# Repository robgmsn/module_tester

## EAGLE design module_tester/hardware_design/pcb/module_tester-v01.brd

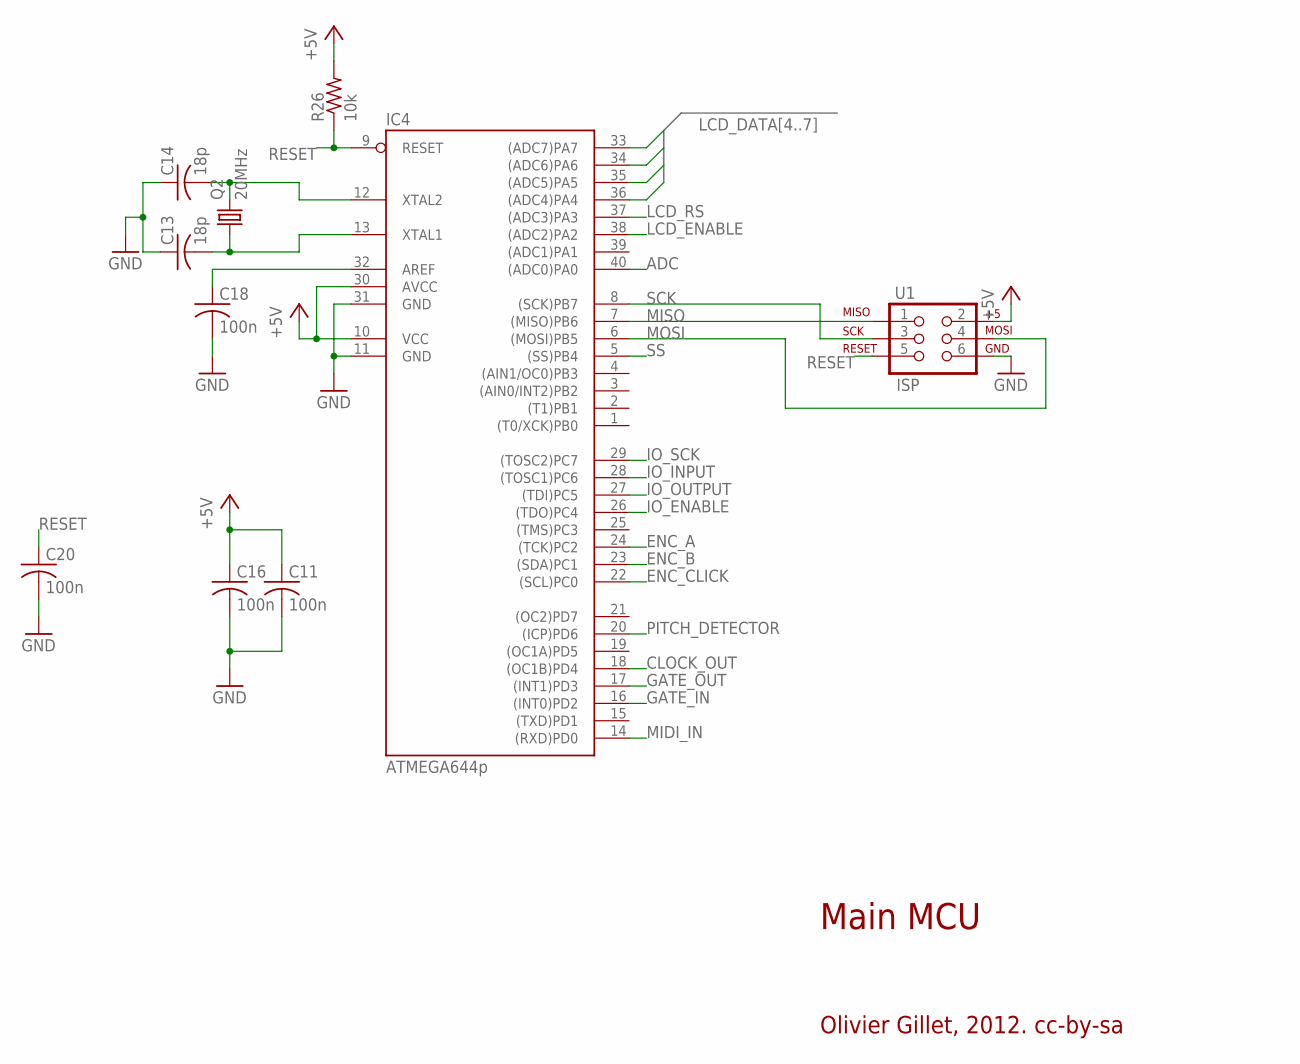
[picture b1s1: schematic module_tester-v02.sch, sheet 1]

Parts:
C11, C16, C18, C20: 100n; C025-025X050
C13, C14: 18p; C025-025X050
IC4: ATMEGA644p; DIL40
Q2: 20MHz; HC49U-V
R26: 10k; 0204/7
U1: ISP; 2X3

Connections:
+5V: C11.1, C16.1, IC4.10 (VCC), IC4.30 (AVCC), R26.2, U1.2; also elsewhere on the board
ADC: IC4.40 ((ADC0)PA0); also elsewhere on the board
CLOCK_OUT: IC4.18 ((OC1B)PD4); also elsewhere on the board
ENC_A: IC4.24 ((TCK)PC2); also elsewhere on the board
ENC_B: IC4.23 ((SDA)PC1); also elsewhere on the board
ENC_CLICK: IC4.22 ((SCL)PC0); also elsewhere on the board
GATE_IN: IC4.16 ((INT0)PD2); also elsewhere on the board
GATE_OUT: IC4.17 ((INT1)PD3); also elsewhere on the board
GND: C11.2, C13.1, C14.1, C16.2, C18.2, C20.2, IC4.11 (GND), IC4.31 (GND), U1.6; also elsewhere on the board
IO_ENABLE: IC4.26 ((TDO)PC4); also elsewhere on the board
IO_INPUT: IC4.28 ((TOSC1)PC6); also elsewhere on the board
IO_OUTPUT: IC4.27 ((TDI)PC5); also elsewhere on the board
IO_SCK: IC4.29 ((TOSC2)PC7); also elsewhere on the board
LCD_DATA4: IC4.36 ((ADC4)PA4); also elsewhere on the board
LCD_DATA5: IC4.35 ((ADC5)PA5); also elsewhere on the board
LCD_DATA6: IC4.34 ((ADC6)PA6); also elsewhere on the board
LCD_DATA7: IC4.33 ((ADC7)PA7); also elsewhere on the board
LCD_ENABLE: IC4.38 ((ADC2)PA2); also elsewhere on the board
LCD_RS: IC4.37 ((ADC3)PA3); also elsewhere on the board
MIDI_IN: IC4.14 ((RXD)PD0); also elsewhere on the board
MISO: IC4.7 ((MISO)PB6), U1.1
MOSI: IC4.6 ((MOSI)PB5), U1.4; also elsewhere on the board
unnamed: C18.1, IC4.32 (AREF)
unnamed: C13.2, IC4.13 (XTAL1), Q2.1
unnamed: C14.2, IC4.12 (XTAL2), Q2.2
PITCH_DETECTOR: IC4.20 ((ICP)PD6); also elsewhere on the board
RESET: C20.1, IC4.9 (RESET), R26.1, U1.5
SCK: IC4.8 ((SCK)PB7), U1.3; also elsewhere on the board
SS: IC4.5 ((SS)PB4); also elsewhere on the board

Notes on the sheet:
Main MCU
Olivier Gillet, 2012. cc-by-sa

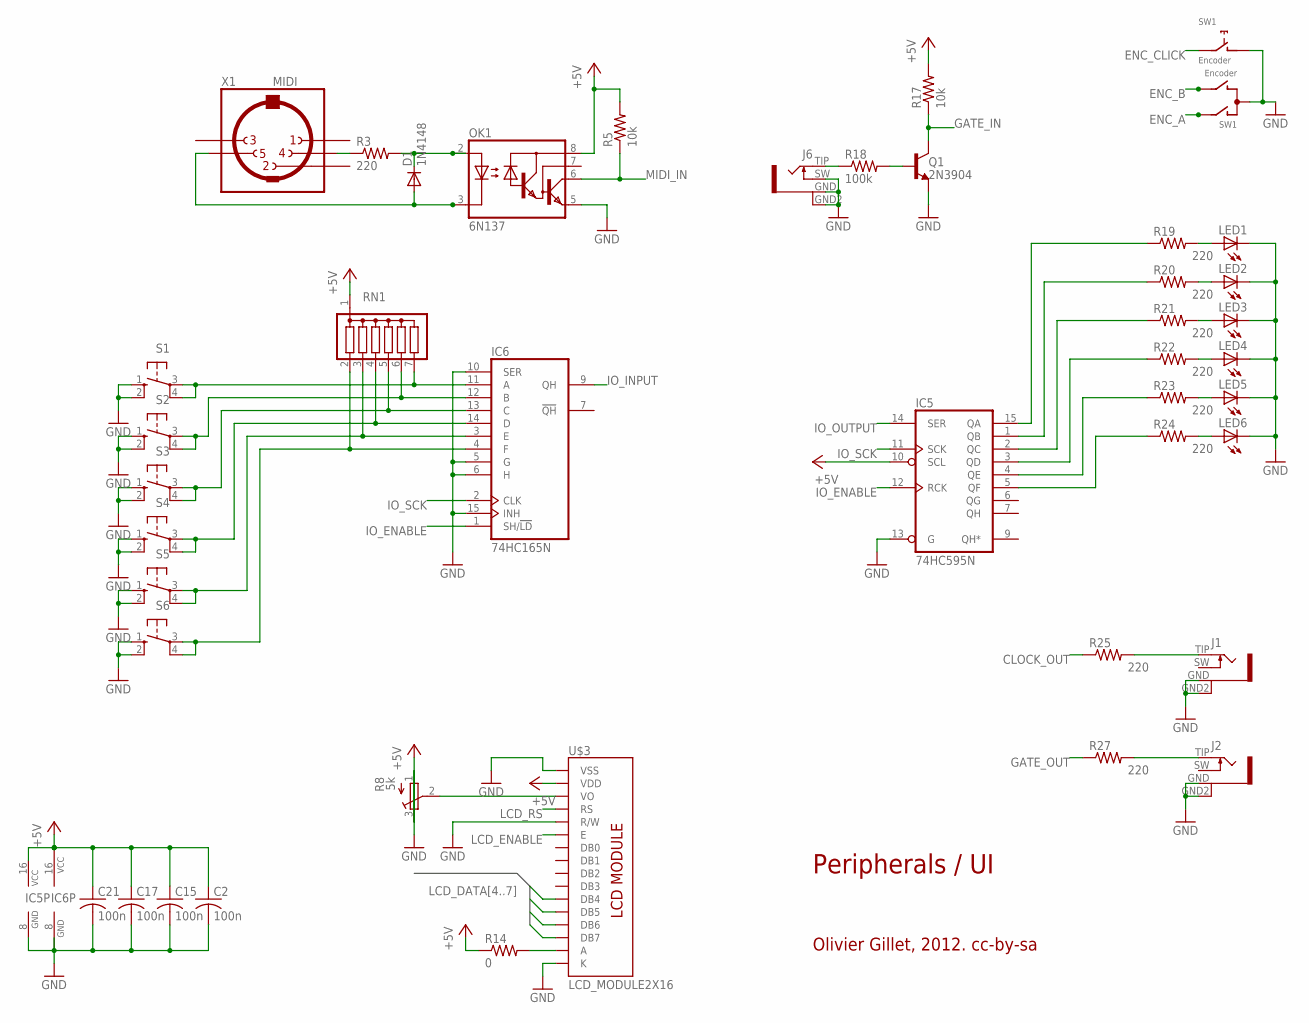
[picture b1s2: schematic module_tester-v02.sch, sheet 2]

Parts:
C2, C15, C17, C21: 100n; C025-025X050
D1: 1N4148; D-5
IC5: 74HC595N; DIL16
IC6: 74HC165N; DIL16
J1, J2, J6: PJ301WQP; WQP_PJ_301BM
LED1, LED2, LED3, LED4, LED5, LED6: LED3MM
OK1: 6N137; DIL08
Q1: 2N3904; TO92-
R3, R19, R20, R21, R22, R23, R24, R25, R27: 220; 0204/7
R5, R17: 10k; 0204/7
R8: 5k; RTRIM3296W
R14: 0; 0204/7
R18: 100k; 0204/7
RN1: G06R; SIL7
S1, S2, S3, S4, S5, S6: 40-XX; B3F-40XX
SW1: Encoder; ALPS_EC12E_SW
U$3: LCD_MODULE2X16; LCD_MODULE_2X16
X1: MIDI; MAB5SH

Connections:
+5V: C2.1, C15.1, C17.1, C21.1, IC5.10 (SCL), IC5.16 (VCC), IC6.16 (VCC), OK1.8 (VCC), R5.2, R8.3 (E), R14.1, R17.2, RN1.1, U$3.2 (VDD); also elsewhere on the board
CLOCK_OUT: R25.1; also elsewhere on the board
ENC_A: SW1.A; also elsewhere on the board
ENC_B: SW1.B; also elsewhere on the board
ENC_CLICK: SW1.E (2); also elsewhere on the board
GATE_IN: Q1.1 (C), R17.1; also elsewhere on the board
GATE_OUT: R27.1; also elsewhere on the board
GND: C2.2, C15.2, C17.2, C21.2, IC5.8 (GND), IC5.13 (G), IC6.5 (G), IC6.6 (H), IC6.8 (GND), IC6.10 (SER), IC6.15 (INH), J1.GND (1), J1.GND2 (4), J2.GND (1), J2.GND2 (4), J6.GND (1), J6.GND2 (4), J6.SW (3), LED1.K (C), LED2.K (C), LED3.K (C), LED4.K (C), LED5.K (C), LED6.K (C), OK1.5 (GND), Q1.3 (E), R8.1 (A), S1.1 (S), S1.2 (S1), S2.1 (S), S2.2 (S1), S3.1 (S), S3.2 (S1), S4.1 (S), S4.2 (S1), S5.1 (S), S5.2 (S1), S6.1 (S), S6.2 (S1), SW1.C, SW1.D (1), U$3.1 (VSS), U$3.5 (R/W), U$3.16 (K); also elsewhere on the board
IO_ENABLE: IC5.12 (RCK), IC6.1 (SH/!LD); also elsewhere on the board
IO_INPUT: IC6.9 (QH); also elsewhere on the board
IO_OUTPUT: IC5.14 (SER); also elsewhere on the board
IO_SCK: IC5.11 (SCK), IC6.2 (CLK); also elsewhere on the board
LCD_DATA4: U$3.11 (DB4); also elsewhere on the board
LCD_DATA5: U$3.12 (DB5); also elsewhere on the board
LCD_DATA6: U$3.13 (DB6); also elsewhere on the board
LCD_DATA7: U$3.14 (DB7); also elsewhere on the board
LCD_ENABLE: U$3.6 (E); also elsewhere on the board
LCD_RS: U$3.4 (RS); also elsewhere on the board
MIDI_IN: OK1.6 (VO), R5.1; also elsewhere on the board
unnamed: IC5.2 (QC), R21.1
unnamed: IC5.4 (QE), R23.1
unnamed: LED5.A, R23.2
unnamed: J6.TIP (2), R18.1
unnamed: IC6.3 (E), RN1.3, S5.3, S5.4 (P1)
unnamed: J1.TIP (2), R25.2
unnamed: IC6.4 (F), RN1.2, S6.3, S6.4 (P1)
unnamed: IC6.14 (D), RN1.4, S4.3, S4.4 (P1)
unnamed: J2.TIP (2), R27.2
unnamed: R8.2 (S), U$3.3 (VO)
unnamed: LED6.A, R24.2
unnamed: IC5.5 (QF), R24.1
unnamed: IC6.11 (A), RN1.7, S1.3, S1.4 (P1)
unnamed: D1.C, OK1.2 (A), R3.2
unnamed: IC5.15 (QA), R19.1
unnamed: IC5.1 (QB), R20.1
unnamed: IC5.3 (QD), R22.1
unnamed: LED1.A, R19.2
unnamed: LED2.A, R20.2
unnamed: LED3.A, R21.2
unnamed: LED4.A, R22.2
unnamed: Q1.2 (B), R18.2
unnamed: R3.1, X1.4
unnamed: D1.A, OK1.3 (C), X1.5
unnamed: R14.2, U$3.15 (A)
unnamed: IC6.12 (B), RN1.6, S2.3, S2.4 (P1)
unnamed: IC6.13 (C), RN1.5, S3.3, S3.4 (P1)

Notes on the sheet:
Peripherals / UI
Olivier Gillet, 2012. cc-by-sa

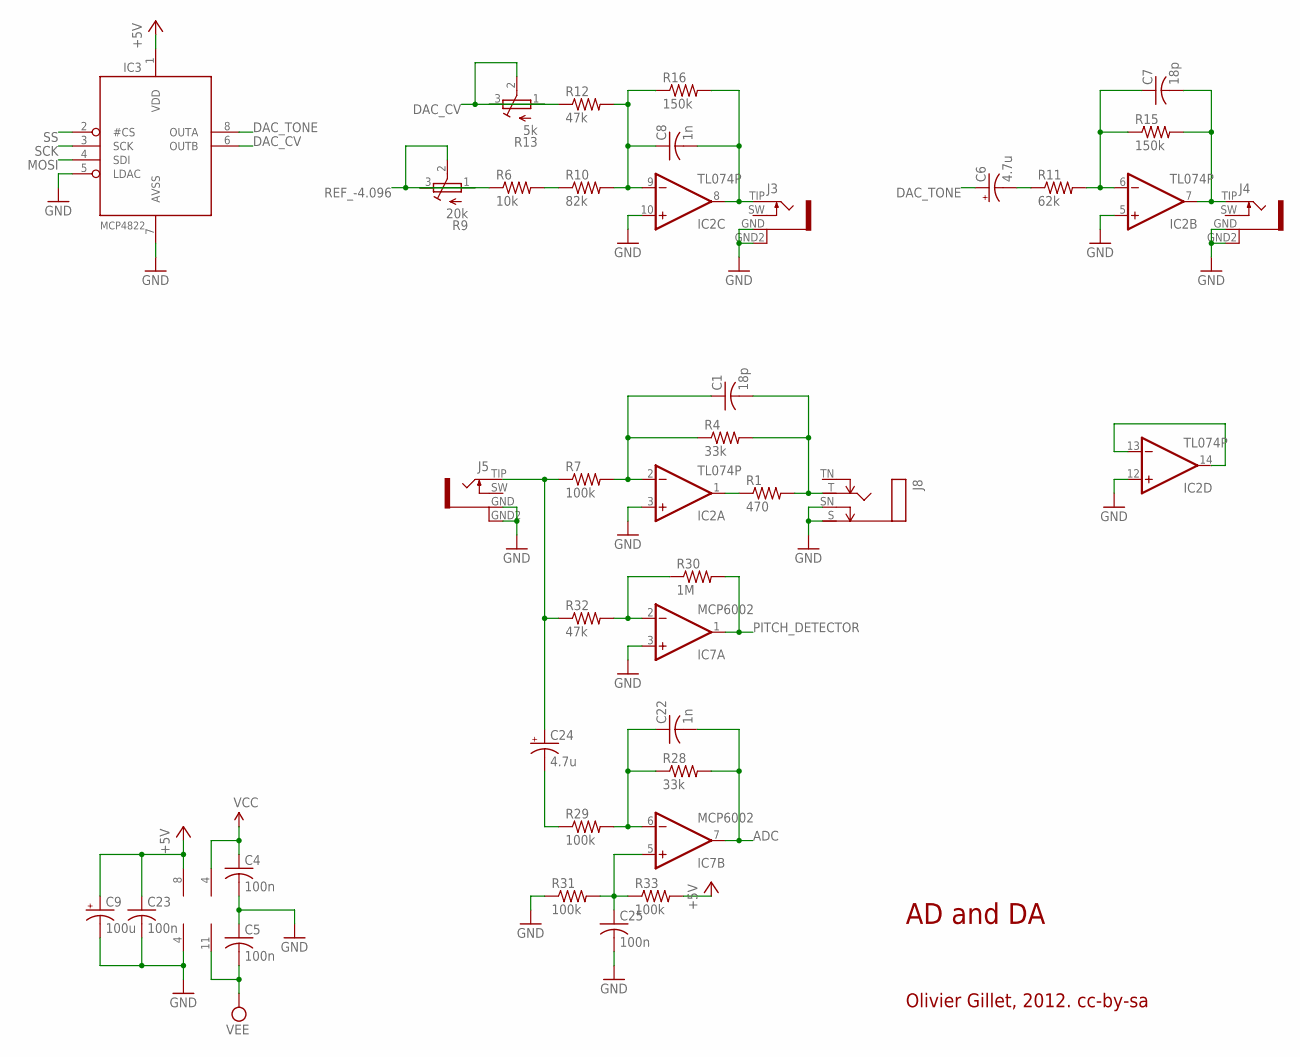
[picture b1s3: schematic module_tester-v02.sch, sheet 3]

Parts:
C1, C7: 18p; C025-025X050
C4, C5, C23, C25: 100n; C025-025X050
C6, C24: 4.7u; E2,5-6
C8, C22: 1n; C025-025X050
C9: 100u; E2,5-7
IC2: TL074P; DIL14
IC3: MCP4822; DIL08
IC7: MCP6002; DIL08
J3, J4, J5: PJ301WQP; WQP_PJ_301BM
J8: MONOSWSLIM; NRJ4HF
R1: 470; 0204/7
R4, R28: 33k; 0204/7
R6: 10k; 0204/7
R7, R29, R31, R33: 100k; 0204/7
R9: 20k; RTRIM3296W
R10: 82k; 0204/7
R11: 62k; 0204/7
R12, R32: 47k; 0204/7
R13: 5k; RTRIM3296W
R15, R16: 150k; 0204/7
R30: 1M; 0204/7

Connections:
+5V: C9.+, C23.1, IC3.1 (VDD), IC7.8 (V+), R33.2; also elsewhere on the board
ADC: C22.2, IC7.7 (OUT), R28.2; also elsewhere on the board
DAC_CV: IC3.6 (OUTB), R13.1 (A), R13.2 (S)
DAC_TONE: C6.+, IC3.8 (OUTA)
GND: C4.2, C5.1, C9.-, C23.2, C25.2, IC2.3 (+IN), IC2.5 (+IN), IC2.10 (+IN), IC2.12 (+IN), IC3.5 (LDAC), IC3.7 (AVSS), IC7.3 (+IN), IC7.4 (V-), J3.GND (1), J3.GND2 (4), J4.GND (1), J4.GND2 (4), J5.GND (1), J5.GND2 (4), J8.S, J8.SN, R31.1; also elsewhere on the board
MOSI: IC3.4 (SDI); also elsewhere on the board
unnamed: C24.+, J5.TIP (2), R7.1, R32.1
unnamed: C1.1, IC2.2 (-IN), R4.1, R7.2
unnamed: C1.2, J8.T, R1.2, R4.2
unnamed: C6.-, R11.1
unnamed: C7.1, IC2.6 (-IN), R11.2, R15.1
unnamed: C8.2, IC2.8 (OUT), J3.TIP (2), R16.2
unnamed: C8.1, IC2.9 (-IN), R10.2, R12.2, R16.1
unnamed: R12.1, R13.3 (E)
unnamed: R6.1, R9.3 (E)
unnamed: R6.2, R10.1
unnamed: C25.1, IC7.5 (+IN), R31.2, R33.1
unnamed: IC7.2 (-IN), R30.1, R32.2
unnamed: C22.1, IC7.6 (-IN), R28.1, R29.2
unnamed: C24.-, R29.1
unnamed: IC2.13 (-IN), IC2.14 (OUT)
unnamed: IC2.1 (OUT), R1.1
PITCH_DETECTOR: IC7.1 (OUT), R30.2; also elsewhere on the board
REF_-4.096: R9.1 (A), R9.2 (S); also elsewhere on the board
SCK: IC3.3 (SCK); also elsewhere on the board
SS: IC3.2 (#CS); also elsewhere on the board
TONE_OUT: C7.2, IC2.7 (OUT), J4.TIP (2), R15.2
VCC: C4.1, IC2.4 (V+); also elsewhere on the board
VEE: C5.2, IC2.11 (V-); also elsewhere on the board

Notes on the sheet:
AD and DA
Olivier Gillet, 2012. cc-by-sa

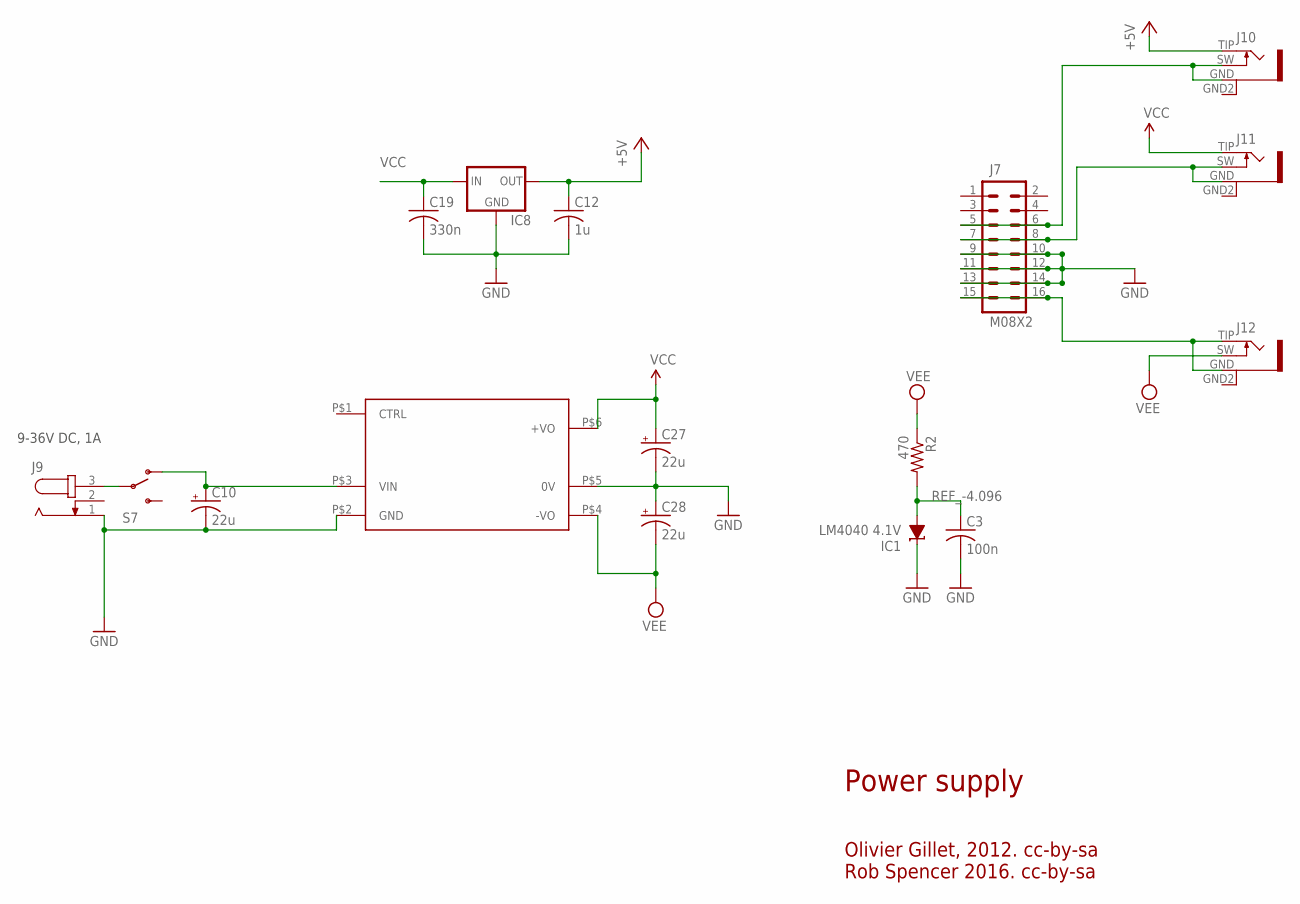
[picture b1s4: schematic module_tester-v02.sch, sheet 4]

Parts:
C3: 100n; C025-025X050
C10, C27, C28: 22u; E2,5-7
C12: 1u; C025-025X050
C19: 330n; C025-025X050
IC1: LM4040 4.1V; LP_O-PBCY-W3
IC8: V_REG_78XX-TO-220; TO-220-ALT
J7: M08X2; 2X8
J9: JACK-PLUG2; SPC4078_BIG_HOLES
J10, J11, J12: PJ301WQP; WQP_PJ_301BM
R2: 470; 0204/7
S7: SWITCH-SPDTPTH; SWITCH-SPDT
U$10: URA241XLD-20WR3

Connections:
+5V: C12.1, IC8.OUT, J10.TIP (2); also elsewhere on the board
GND: C3.2, C10.-, C12.2, C19.2, C27.-, C28.+, IC1.2 (C), IC8.GND, J7.9, J7.10, J7.11, J7.12, J7.13, J7.14, J9.1, U$10.P$2 (GND), U$10.P$5 (0V); also elsewhere on the board
unnamed: J9.3, S7.2
unnamed: J7.5, J7.6, J10.GND (1), J10.SW (3)
unnamed: J7.7, J7.8, J11.GND (1), J11.SW (3)
unnamed: C10.+, S7.1 (O), U$10.P$3 (VIN)
unnamed: J7.15, J7.16, J12.GND (1), J12.TIP (2)
REF_-4.096: C3.1, IC1.3 (A), R2.2; also elsewhere on the board
VCC: C19.1, C27.+, IC8.IN, J11.TIP (2), U$10.P$6 (+VO); also elsewhere on the board
VEE: C28.-, J12.SW (3), R2.1, U$10.P$4 (-VO); also elsewhere on the board

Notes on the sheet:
9-36V DC, 1A
Power supply
Olivier Gillet, 2012. cc-by-sa Rob Spencer 2016. cc-by-sa

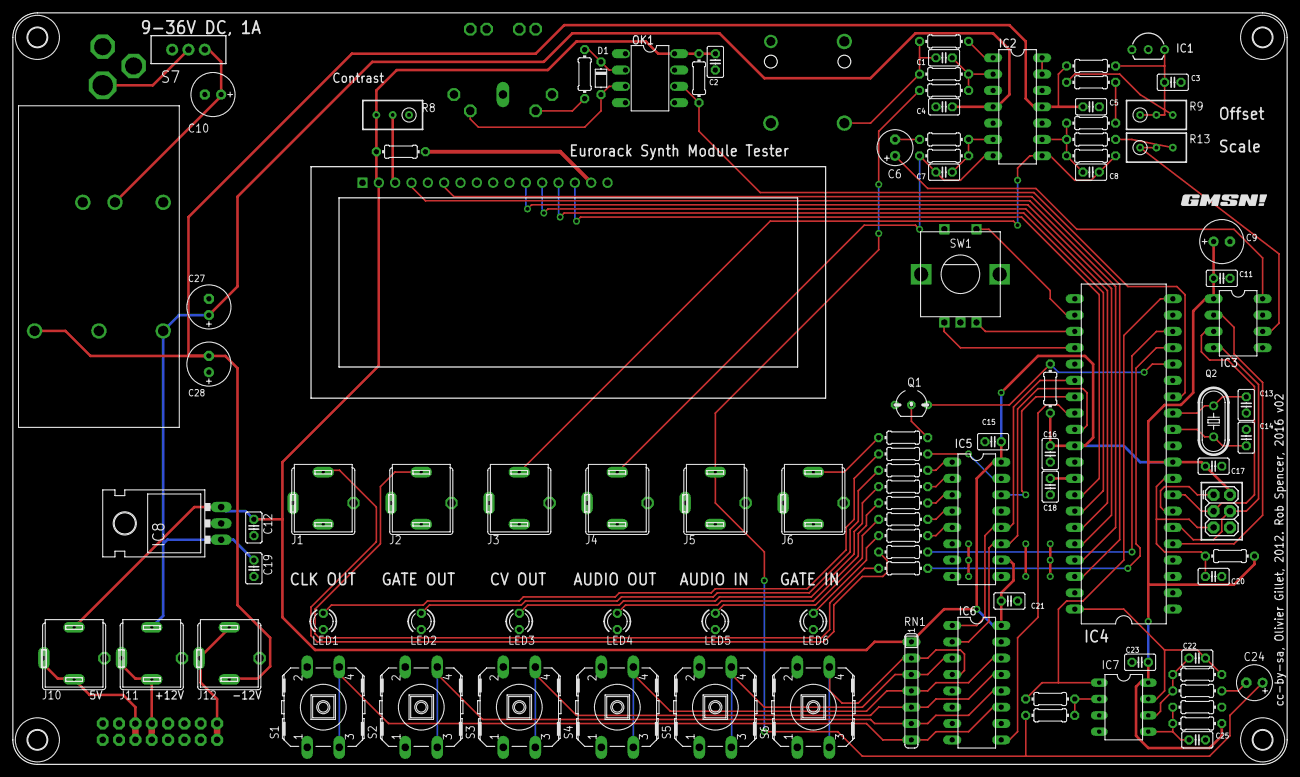
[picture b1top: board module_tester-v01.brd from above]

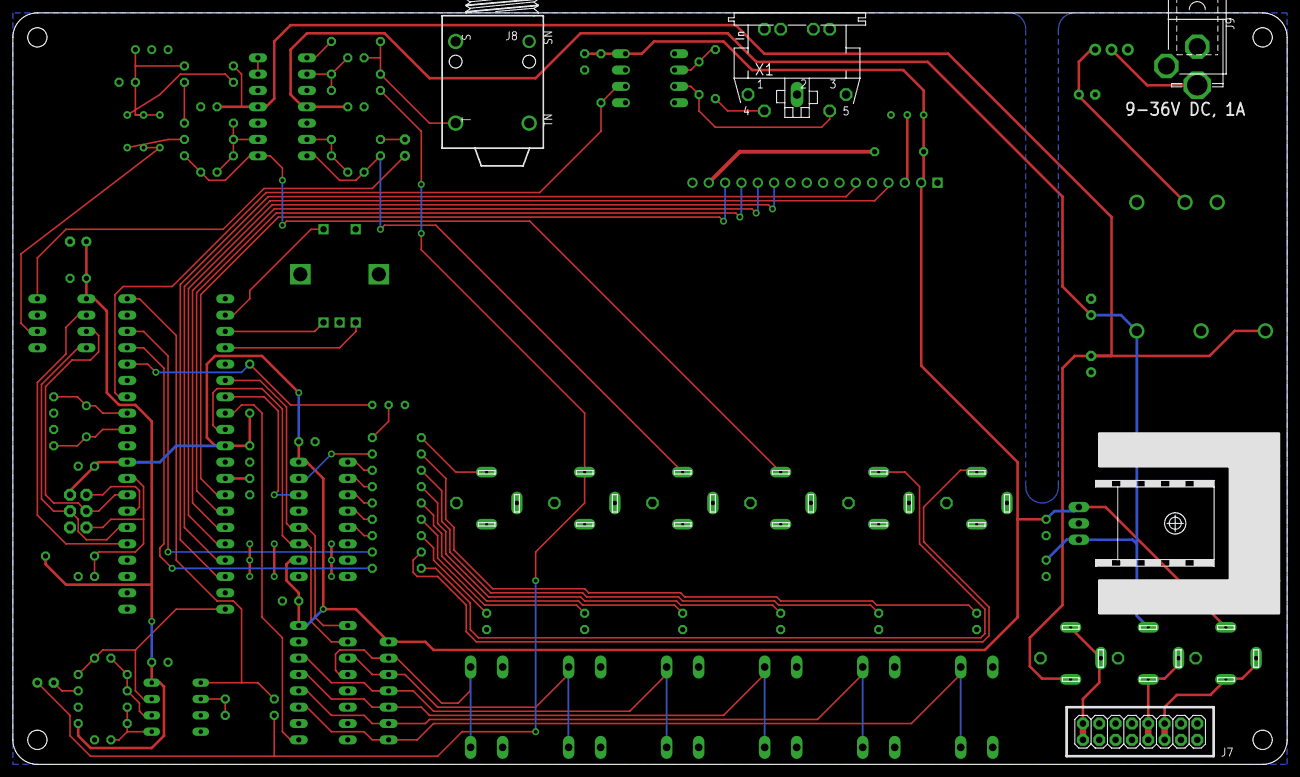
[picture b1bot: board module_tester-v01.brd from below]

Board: 2 copper layers, 198.1 x 116.8 mm, 110 parts (5 on the bottom side), 83 nets.

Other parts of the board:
U$1, U$2, U$5, U$6: 3,0
U$4: V2_LOGO_DINGBAT1
U$7: D02A-L
U$8: GMSN!_LOGO

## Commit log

2016-08-06 Add files via upload
    Converter power supply to DC and added jacks for ammeter.
2016-08-06 DCDC Converter and Ammeter Jacks

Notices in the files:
module_tester/hardware_design/pcb/module_tester-v01.brd:
cc-by-sa, Olivier Gillet, 2012. Rob Spencer, 2016 v02
parts and their libraries:
SparkFun-Electromechanical: Licensing: CC v3.0 Share-Alike You are welcome to use this library for commercial purposes.
